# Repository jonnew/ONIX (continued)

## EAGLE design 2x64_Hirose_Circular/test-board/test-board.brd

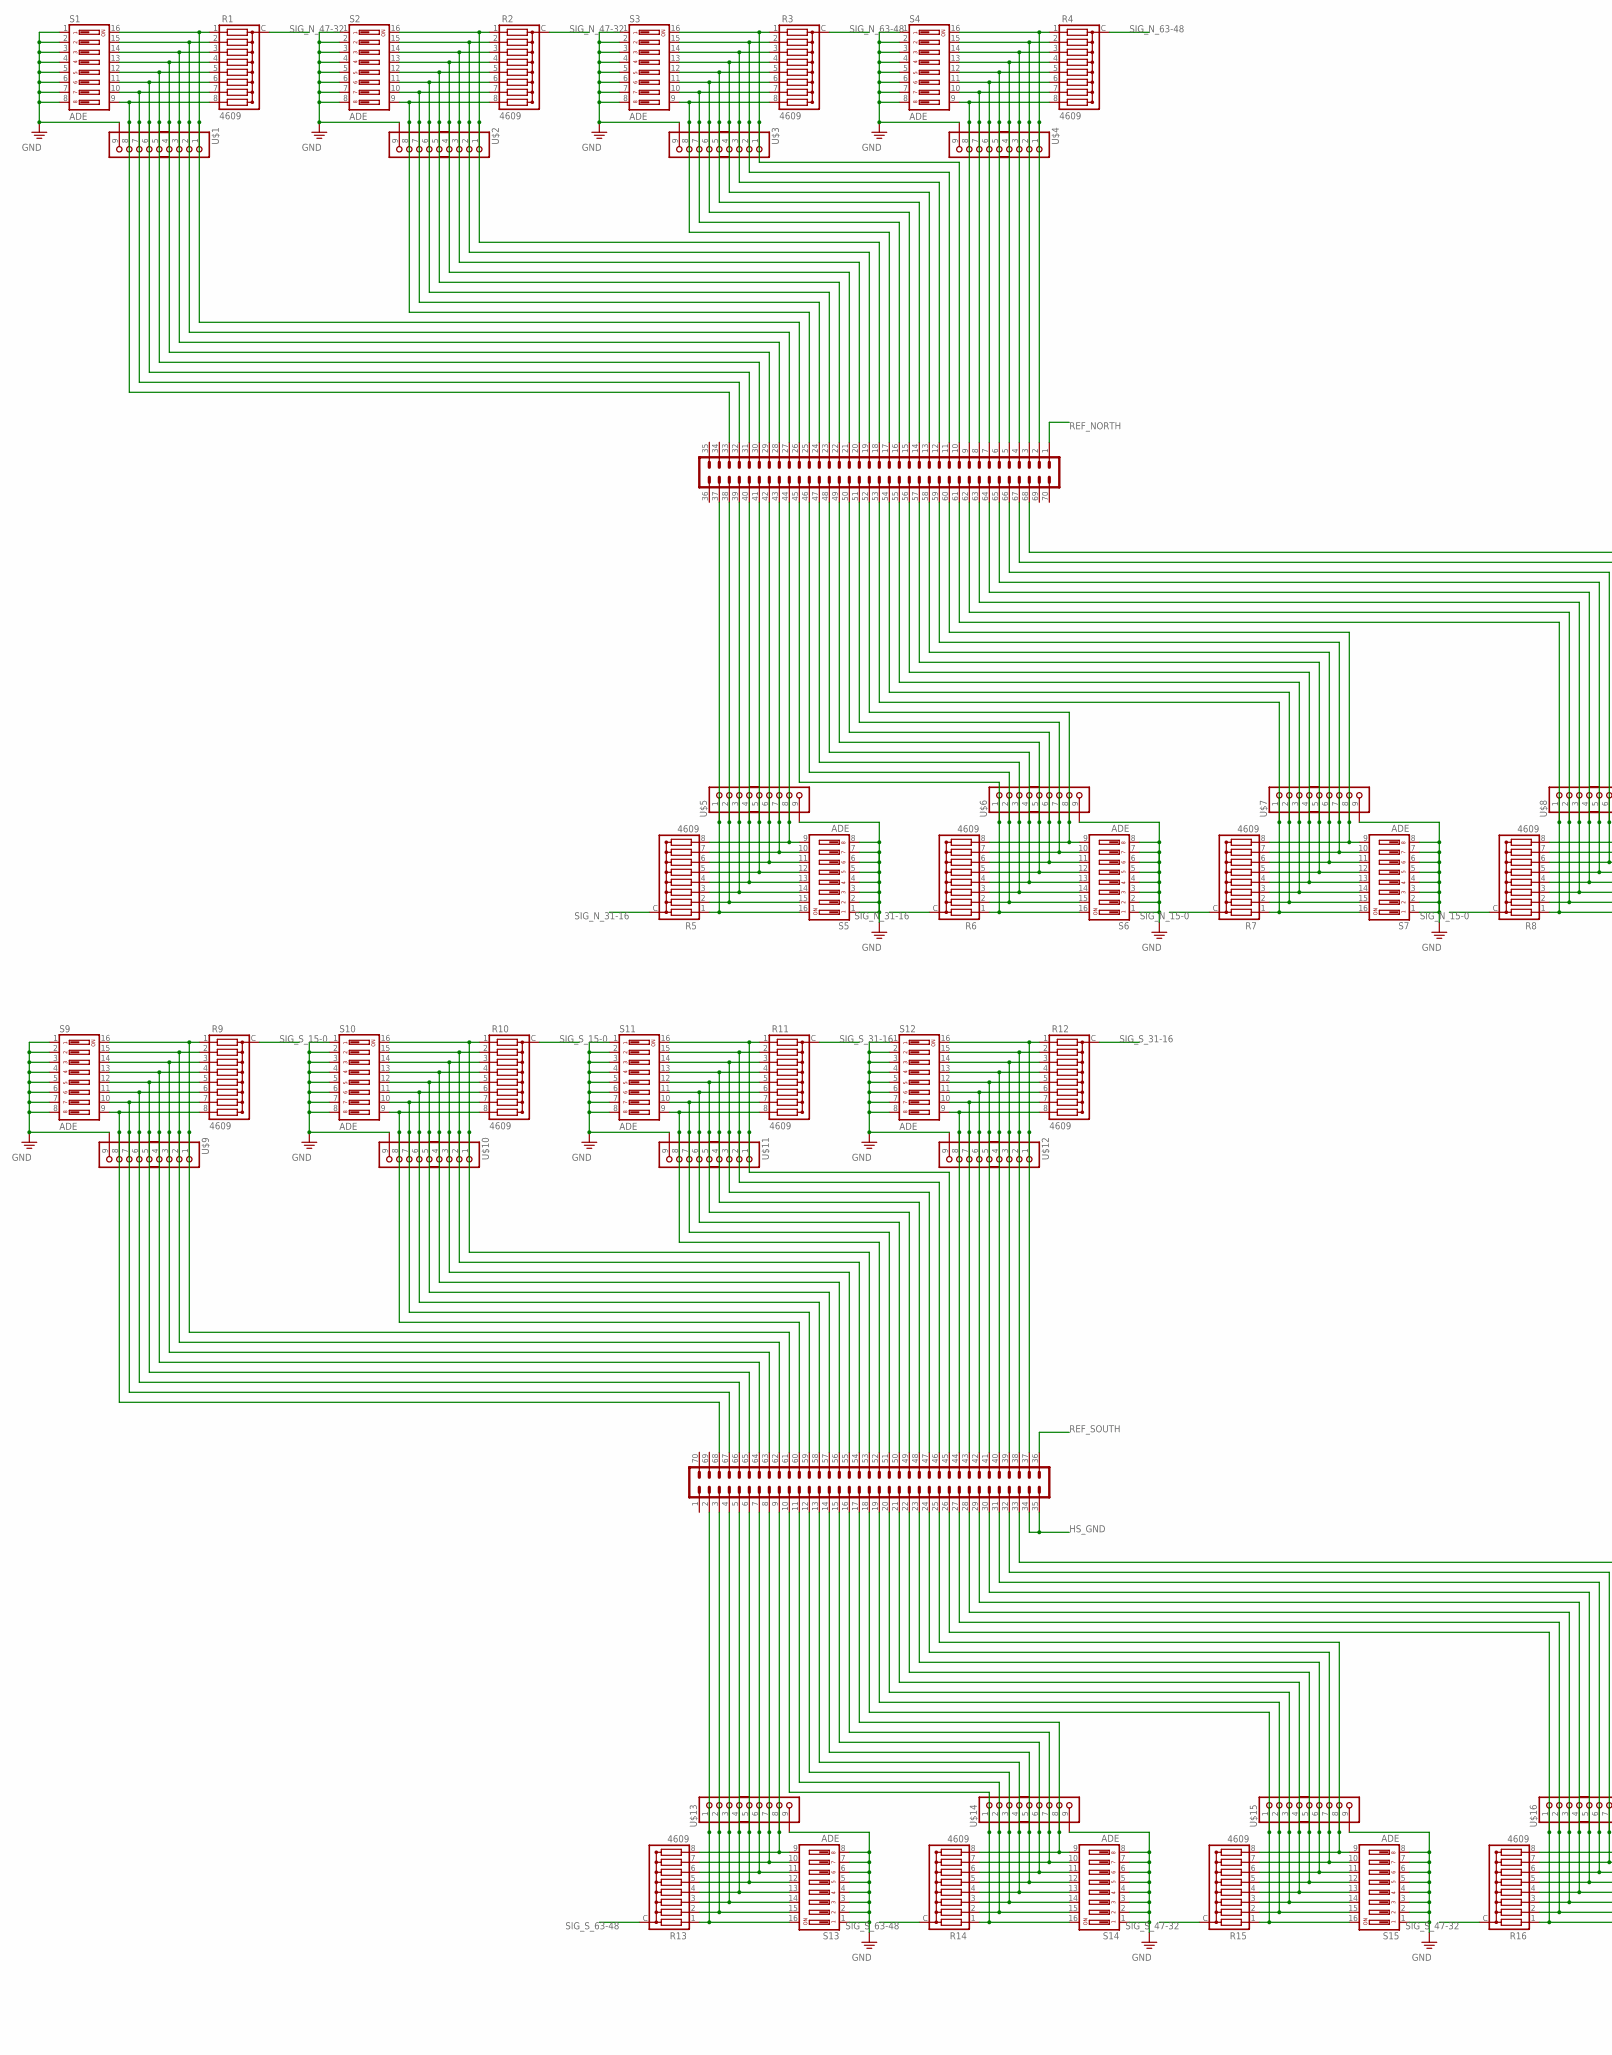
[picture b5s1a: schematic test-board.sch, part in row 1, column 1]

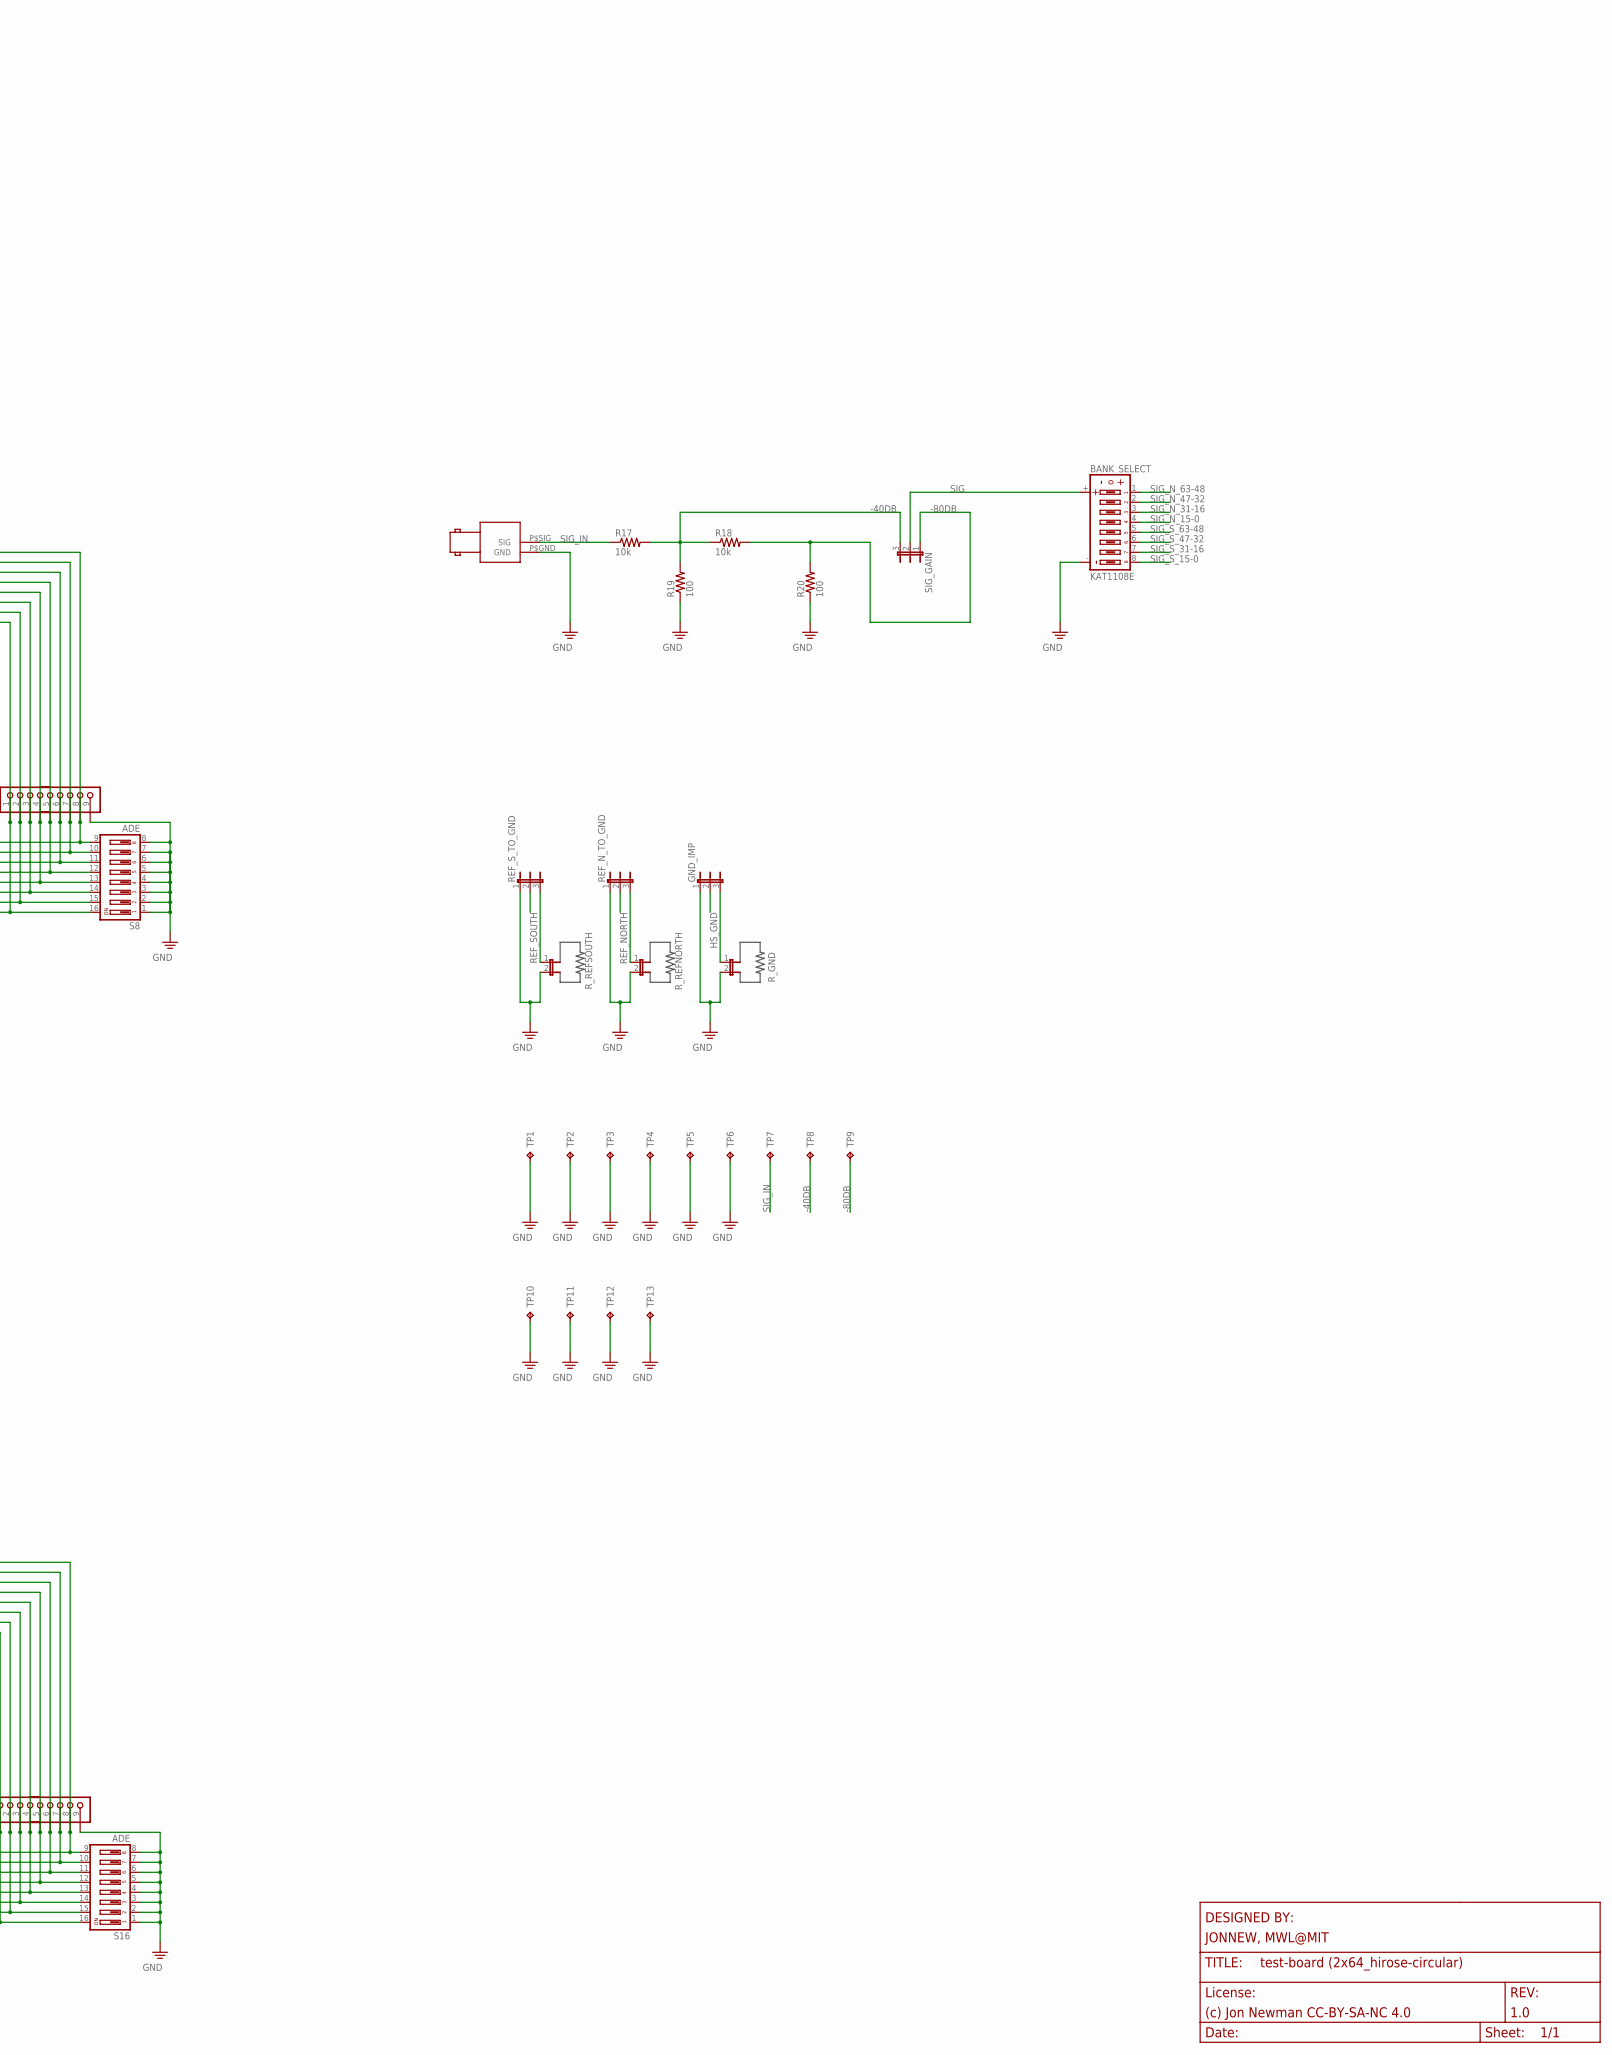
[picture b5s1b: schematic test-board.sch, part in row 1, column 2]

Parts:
AIN_N0T: DF40HEAD; DF40-70HEAD
AIN_S0T: DF40HEAD; DF40-70HEAD
BANK_SELECT: KAT1108E; 206-124_DIP8-SPDT
GND_IMP: JP3E; JP3
R1, R2, R3, R4, R5, R6, R7, R8, R9, R10, R11, R12, R13, R14, R15, R16: 4609; RNX8-0.1
R17, R18: 10k; 0805
R19, R20: 100; 0805
REF_N_TO_GND: JP3E; JP3
REF_S_TO_GND: JP3E; JP3
R_GND: JP2E_THRU-HOLE; JP2
R_REFNORTH: JP2E_THRU-HOLE; JP2
R_REFSOUTH: JP2E_THRU-HOLE; JP2
S1, S2, S3, S4, S5, S6, S7, S8, S9, S10, S11, S12, S13, S14, S15, S16: ADE; ADE_DIP8-SPST
SIG_GAIN: JP3E; JP3
SIG_IN: 1-1634622-0; BNC_RIGHT_ANGLE
TP1, TP2, TP3, TP4, TP5, TP6: GND; P1-20
TP7: SIG_IN; P1-20
TP8: -40dB; P1-20
TP9: -80dB; P1-20
TP10, TP11, TP12, TP13: TP_4-40; 4-40_PLATED
U$1, U$2, U$3, U$4, U$5, U$6, U$7, U$8, U$9, U$10, U$11, U$12, U$13, U$14, U$15, U$16: PINHD-1X9; 1X09

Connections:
-40DB: R17.2, R18.1, R19.2, SIG_GAIN.3, TP8.TP
-80DB: R18.2, R20.2, SIG_GAIN.1, TP9.TP
GND: BANK_SELECT.-, GND_IMP.1, R19.1, R20.1, REF_N_TO_GND.1, REF_S_TO_GND.1, R_GND.2, R_REFNORTH.2, R_REFSOUTH.2, S1.1, S1.2, S1.3, S1.4, S1.5, S1.6, S1.7, S1.8, S2.1, S2.2, S2.3, S2.4, S2.5, S2.6, S2.7, S2.8, S3.1, S3.2, S3.3, S3.4, S3.5, S3.6, S3.7, S3.8, S4.1, S4.2, S4.3, S4.4, S4.5, S4.6, S4.7, S4.8, S5.1, S5.2, S5.3, S5.4, S5.5, S5.6, S5.7, S5.8, S6.1, S6.2, S6.3, S6.4, S6.5, S6.6, S6.7, S6.8, S7.1, S7.2, S7.3, S7.4, S7.5, S7.6, S7.7, S7.8, S8.1, S8.2, S8.3, S8.4, S8.5, S8.6, S8.7, S8.8, S9.1, S9.2, S9.3, S9.4, S9.5, S9.6, S9.7, S9.8, S10.1, S10.2, S10.3, S10.4, S10.5, S10.6, S10.7, S10.8, S11.1, S11.2, S11.3, S11.4, S11.5, S11.6, S11.7, S11.8, S12.1, S12.2, S12.3, S12.4, S12.5, S12.6, S12.7, S12.8, S13.1, S13.2, S13.3, S13.4, S13.5, S13.6, S13.7, S13.8, S14.1, S14.2, S14.3, S14.4, S14.5, S14.6, S14.7, S14.8, S15.1, S15.2, S15.3, S15.4, S15.5, S15.6, S15.7, S15.8, S16.1, S16.2, S16.3, S16.4, S16.5, S16.6, S16.7, S16.8, SIG_IN.P$GND (GND), TP1.TP, TP2.TP, TP3.TP, TP4.TP, TP5.TP, TP6.TP, TP10.P$1, TP11.P$1, TP12.P$1, TP13.P$1, U$1.9, U$2.9, U$3.9, U$4.9, U$5.9, U$6.9, U$7.9, U$8.9, U$9.9, U$10.9, U$11.9, U$12.9, U$13.9, U$14.9, U$15.9, U$16.9
HS_GND: AIN_S0T.34, AIN_S0T.35, GND_IMP.2
unnamed: GND_IMP.3, R_GND.1
unnamed: AIN_S0T.3, R13.2, S13.15, U$13.2
unnamed: AIN_S0T.5, R13.4, S13.13, U$13.4
unnamed: AIN_N0T.17, R3.8, S3.9, U$3.8
unnamed: AIN_N0T.9, R4.8, S4.9, U$4.8
unnamed: AIN_N0T.15, R3.6, S3.11, U$3.6
unnamed: AIN_N0T.14, R3.5, S3.12, U$3.5
unnamed: AIN_N0T.3, R4.2, S4.15, U$4.2
unnamed: AIN_N0T.12, R3.3, S3.14, U$3.3
unnamed: AIN_N0T.4, R4.3, S4.14, U$4.3
unnamed: AIN_N0T.10, R3.1, S3.16, U$3.1
unnamed: REF_N_TO_GND.3, R_REFNORTH.1
unnamed: AIN_N0T.7, R4.6, S4.11, U$4.6
unnamed: AIN_N0T.8, R4.7, S4.10, U$4.7
unnamed: AIN_N0T.6, R4.5, S4.12, U$4.5
unnamed: AIN_N0T.2, R4.1, S4.16, U$4.1
unnamed: AIN_N0T.27, R1.2, S1.15, U$1.2
unnamed: AIN_N0T.29, R1.4, S1.13, U$1.4
unnamed: AIN_N0T.43, R5.7, S5.10, U$5.7
unnamed: AIN_S0T.7, R13.6, S13.11, U$13.6
unnamed: AIN_N0T.32, R1.7, S1.10, U$1.7
unnamed: REF_S_TO_GND.3, R_REFSOUTH.1
unnamed: AIN_N0T.30, R1.5, S1.12, U$1.5
unnamed: AIN_N0T.41, R5.5, S5.12, U$5.5
unnamed: AIN_N0T.28, R1.3, S1.14, U$1.3
unnamed: AIN_S0T.9, R13.8, S13.9, U$13.8
unnamed: AIN_N0T.39, R5.3, S5.14, U$5.3
unnamed: AIN_N0T.31, R1.6, S1.11, U$1.6
unnamed: AIN_S0T.10, R14.1, S14.16, U$14.1
unnamed: AIN_N0T.33, R1.8, S1.9, U$1.8
unnamed: AIN_N0T.37, R5.1, S5.16, U$5.1
unnamed: AIN_N0T.19, R2.2, S2.15, U$2.2
unnamed: AIN_N0T.52, R6.8, S6.9, U$6.8
unnamed: AIN_N0T.21, R2.4, S2.13, U$2.4
unnamed: AIN_S0T.11, R14.2, S14.15, U$14.2
unnamed: AIN_N0T.23, R2.6, S2.11, U$2.6
unnamed: AIN_N0T.24, R2.7, S2.10, U$2.7
unnamed: AIN_S0T.14, R14.5, S14.12, U$14.5
unnamed: AIN_S0T.15, R14.6, S14.11, U$14.6
unnamed: AIN_N0T.47, R6.3, S6.14, U$6.3
unnamed: AIN_S0T.16, R14.7, S14.10, U$14.7
unnamed: AIN_S0T.19, R15.2, S15.15, U$15.2
unnamed: AIN_S0T.20, R15.3, S15.14, U$15.3
unnamed: AIN_S0T.21, R15.4, S15.13, U$15.4
unnamed: AIN_S0T.22, R15.5, S15.12, U$15.5
unnamed: AIN_S0T.23, R15.6, S15.11, U$15.6
unnamed: AIN_S0T.24, R15.7, S15.10, U$15.7
unnamed: AIN_S0T.25, R15.8, S15.9, U$15.8
unnamed: AIN_S0T.26, R16.1, S16.16, U$16.1
unnamed: AIN_N0T.53, R7.1, S7.16, U$7.1
unnamed: AIN_S0T.27, R16.2, S16.15, U$16.2
unnamed: AIN_S0T.28, R16.3, S16.14, U$16.3
unnamed: AIN_S0T.29, R16.4, S16.13, U$16.4
unnamed: AIN_S0T.30, R16.5, S16.12, U$16.5
unnamed: AIN_S0T.31, R16.6, S16.11, U$16.6
unnamed: AIN_S0T.32, R16.7, S16.10, U$16.7
unnamed: AIN_S0T.33, R16.8, S16.9, U$16.8
unnamed: AIN_S0T.8, R13.7, S13.10, U$13.7
unnamed: AIN_S0T.6, R13.5, S13.12, U$13.5
unnamed: AIN_S0T.4, R13.3, S13.14, U$13.3
unnamed: AIN_S0T.2, R13.1, S13.16, U$13.1
unnamed: AIN_S0T.17, R14.8, S14.9, U$14.8
unnamed: AIN_S0T.12, R14.3, S14.14, U$14.3
unnamed: AIN_S0T.18, R15.1, S15.16, U$15.1
unnamed: AIN_S0T.61, R9.1, S9.16, U$9.1
unnamed: AIN_S0T.60, R10.8, S10.9, U$10.8
unnamed: AIN_S0T.57, R10.5, S10.12, U$10.5
unnamed: AIN_S0T.55, R10.3, S10.14, U$10.3
unnamed: AIN_S0T.53, R10.1, S10.16, U$10.1
unnamed: AIN_S0T.51, R11.7, S11.10, U$11.7
unnamed: AIN_S0T.48, R11.4, S11.13, U$11.4
unnamed: AIN_S0T.46, R11.2, S11.15, U$11.2
unnamed: AIN_S0T.40, R12.4, S12.13, U$12.4
unnamed: AIN_S0T.52, R11.8, S11.9, U$11.8
unnamed: AIN_S0T.50, R11.6, S11.11, U$11.6
unnamed: AIN_S0T.49, R11.5, S11.12, U$11.5
unnamed: AIN_S0T.47, R11.3, S11.14, U$11.3
unnamed: AIN_S0T.45, R11.1, S11.16, U$11.1
unnamed: AIN_S0T.67, R9.7, S9.10, U$9.7
unnamed: AIN_S0T.65, R9.5, S9.12, U$9.5
unnamed: AIN_S0T.63, R9.3, S9.14, U$9.3
unnamed: AIN_S0T.44, R12.8, S12.9, U$12.8
unnamed: AIN_S0T.38, R12.2, S12.15, U$12.2
unnamed: AIN_S0T.39, R12.3, S12.14, U$12.3
unnamed: AIN_S0T.42, R12.6, S12.11, U$12.6
unnamed: AIN_S0T.43, R12.7, S12.10, U$12.7
unnamed: AIN_S0T.41, R12.5, S12.12, U$12.5
unnamed: AIN_S0T.37, R12.1, S12.16, U$12.1
unnamed: AIN_S0T.64, R9.4, S9.13, U$9.4
unnamed: AIN_S0T.66, R9.6, S9.11, U$9.6
unnamed: AIN_S0T.68, R9.8, S9.9, U$9.8
unnamed: AIN_S0T.54, R10.2, S10.15, U$10.2
unnamed: AIN_S0T.56, R10.4, S10.13, U$10.4
unnamed: AIN_S0T.58, R10.6, S10.11, U$10.6
unnamed: AIN_S0T.59, R10.7, S10.10, U$10.7
unnamed: AIN_S0T.13, R14.4, S14.13, U$14.4
unnamed: AIN_S0T.62, R9.2, S9.15, U$9.2
unnamed: AIN_N0T.26, R1.1, S1.16, U$1.1
unnamed: AIN_N0T.25, R2.8, S2.9, U$2.8
unnamed: AIN_N0T.22, R2.5, S2.12, U$2.5
unnamed: AIN_N0T.20, R2.3, S2.14, U$2.3
unnamed: AIN_N0T.18, R2.1, S2.16, U$2.1
unnamed: AIN_N0T.16, R3.7, S3.10, U$3.7
unnamed: AIN_N0T.13, R3.4, S3.13, U$3.4
unnamed: AIN_N0T.11, R3.2, S3.15, U$3.2
unnamed: AIN_N0T.5, R4.4, S4.13, U$4.4
unnamed: AIN_N0T.38, R5.2, S5.15, U$5.2
unnamed: AIN_N0T.40, R5.4, S5.13, U$5.4
unnamed: AIN_N0T.42, R5.6, S5.11, U$5.6
unnamed: AIN_N0T.44, R5.8, S5.9, U$5.8
unnamed: AIN_N0T.45, R6.1, S6.16, U$6.1
unnamed: AIN_N0T.46, R6.2, S6.15, U$6.2
unnamed: AIN_N0T.48, R6.4, S6.13, U$6.4
unnamed: AIN_N0T.49, R6.5, S6.12, U$6.5
unnamed: AIN_N0T.50, R6.6, S6.11, U$6.6
unnamed: AIN_N0T.51, R6.7, S6.10, U$6.7
unnamed: AIN_N0T.54, R7.2, S7.15, U$7.2
unnamed: AIN_N0T.55, R7.3, S7.14, U$7.3
unnamed: AIN_N0T.56, R7.4, S7.13, U$7.4
unnamed: AIN_N0T.57, R7.5, S7.12, U$7.5
unnamed: AIN_N0T.58, R7.6, S7.11, U$7.6
unnamed: AIN_N0T.59, R7.7, S7.10, U$7.7
unnamed: AIN_N0T.60, R7.8, S7.9, U$7.8
unnamed: AIN_N0T.61, R8.1, S8.16, U$8.1
unnamed: AIN_N0T.62, R8.2, S8.15, U$8.2
unnamed: AIN_N0T.63, R8.3, S8.14, U$8.3
unnamed: AIN_N0T.64, R8.4, S8.13, U$8.4
unnamed: AIN_N0T.65, R8.5, S8.12, U$8.5
unnamed: AIN_N0T.66, R8.6, S8.11, U$8.6
unnamed: AIN_N0T.67, R8.7, S8.10, U$8.7
unnamed: AIN_N0T.68, R8.8, S8.9, U$8.8
REF_NORTH: AIN_N0T.1, REF_N_TO_GND.2
REF_SOUTH: AIN_S0T.36, REF_S_TO_GND.2
SIG: BANK_SELECT.+, SIG_GAIN.2
SIG_IN: R17.1, SIG_IN.P$SIG (SIG), TP7.TP
SIG_N_15-0: BANK_SELECT.4, R7.C, R8.C
SIG_N_31-16: BANK_SELECT.3, R5.C, R6.C
SIG_N_47-32: BANK_SELECT.2, R1.C, R2.C
SIG_N_63-48: BANK_SELECT.1, R3.C, R4.C
SIG_S_15-0: BANK_SELECT.8, R9.C, R10.C
SIG_S_31-16: BANK_SELECT.7, R11.C, R12.C
SIG_S_47-32: BANK_SELECT.6, R15.C, R16.C
SIG_S_63-48: BANK_SELECT.5, R13.C, R14.C

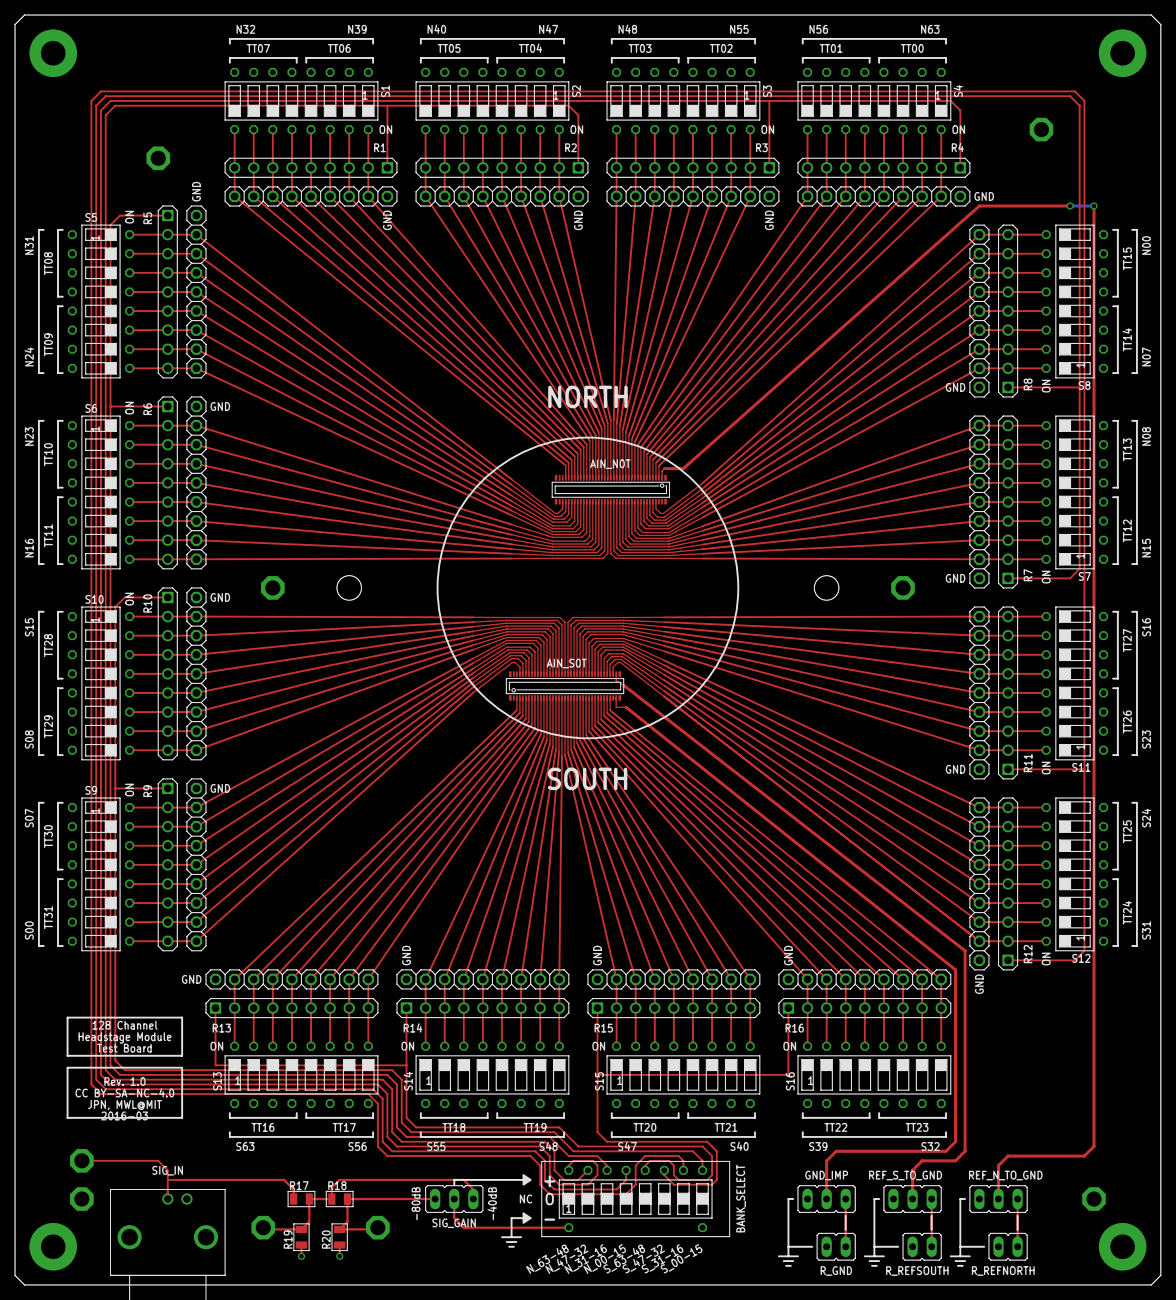
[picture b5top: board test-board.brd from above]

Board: 2 copper layers, 152.4 x 168.9 mm, 76 parts (0 on the bottom side), 147 nets.
